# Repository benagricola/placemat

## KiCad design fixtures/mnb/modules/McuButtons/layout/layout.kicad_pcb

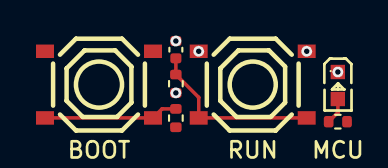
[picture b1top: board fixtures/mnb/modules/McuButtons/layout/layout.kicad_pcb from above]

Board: 2 copper layers, 7 parts (0 on the bottom side), 5 nets.

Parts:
C1: 100nF; C_0402_1005Metric
D1: KT-0603B; LED0603-RD_C2288
R1, R3: ERJ-2RKF1001X; R_0402_1005Metric
R2: ERJ-2RKF1800X; R_0402_1005Metric
SW1, SW2: TS-1187A-B-A-B; SW-SMD_4P-L5.1-W5.1-P3.70-LS6.5-TL_H1.5

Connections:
BOOT_SW: R1.2, SW1.1, SW1.2
STATUS_LED_A: D1.2, R2.2
boot_com: SW1.3, SW1.4
gnd: C1.1, D1.1, SW2.3, SW2.4
run: C1.2, R3.2, SW2.1, SW2.2

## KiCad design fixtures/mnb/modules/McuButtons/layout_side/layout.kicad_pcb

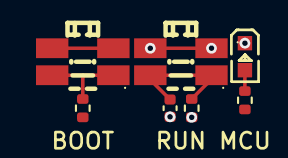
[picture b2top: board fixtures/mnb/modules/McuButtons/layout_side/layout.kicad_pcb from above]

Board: 2 copper layers, 7 parts (0 on the bottom side), 5 nets.

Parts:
C1: 100nF; C_0402_1005Metric
D1: KT-0603B; LED0603-RD_C2288
R1, R3: ERJ-2RKF1001X; R_0402_1005Metric
R2: ERJ-2RKF1800X; R_0402_1005Metric
SW1, SW2: EVQP7J01P; SW-SMD_EVQP7J01P

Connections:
BOOT_SW: R1.2, SW1.1, SW1.1'
STATUS_LED_A: D1.2, R2.2
boot_com: SW1.2, SW1.2'
gnd: C1.1, D1.1, SW2.2, SW2.2'
run: C1.2, R3.2, SW2.1, SW2.1'

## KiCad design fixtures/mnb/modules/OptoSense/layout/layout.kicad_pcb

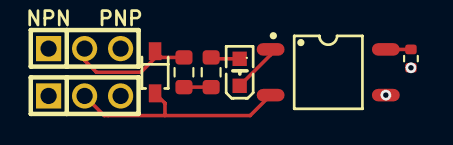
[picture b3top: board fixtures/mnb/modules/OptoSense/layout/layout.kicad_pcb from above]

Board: 2 copper layers, 8 parts (0 on the bottom side), 7 nets.

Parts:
D1: 1N4148WS; SOD-323_L1.8-W1.3-LS2.5-RD
D2: KT-0603Y; LED0603-R-RD_C2287
H1, H2: PZ200V-11-03P; HDR-TH_3P-P2.00-V-M
R1: ERJ-2RKF1002X; R_0402_1005Metric
R2, R3: ERJ-3EKF2201V; R_0603_1608Metric
U1: LTV-357T-C; SOP-4_L4.4-W3.9-P2.54-LS7.0-TL

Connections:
OPTO_AN: D2.2, U1.1
OPTO_ANSRC: D1.1, H1.2, R2.1
OPTO_CAT: D1.2, H2.2, U1.2
OPTO_LEDA: D2.1, R3.2
OPTO_RMID: R2.2, R3.1
gnd: H2.3, U1.3
out: R1.1, U1.4

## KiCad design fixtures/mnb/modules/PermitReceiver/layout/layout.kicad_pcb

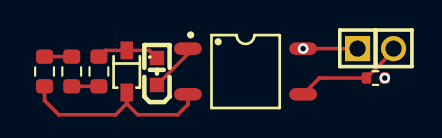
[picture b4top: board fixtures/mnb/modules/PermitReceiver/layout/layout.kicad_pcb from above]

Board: 2 copper layers, 8 parts (0 on the bottom side), 7 nets.

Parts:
D1: 1N4148WS; SOD-323_L1.8-W1.3-LS2.5-RD
D2: KT-0603R; LED-SMD_L1.6-W0.8-R-RD
H1: PZ200V-11-02P; HDR-TH_2P-P2.00-V-M
R1: ERJ-3EKF1002V; R_0603_1608Metric
R2: ERJ-2RKF1002X; R_0402_1005Metric
R3, R4: ERJ-3EKF2201V; R_0603_1608Metric
U1: LTV-357T-C; SOP-4_L4.4-W3.9-P2.54-LS7.0-TL

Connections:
PERMIT_AN: D1.1, D2.1, R4.2
PERMIT_OPTO_AN: D2.2, U1.1
PERMIT_RMID: R3.2, R4.1
out: H1.2, R2.1, U1.3
perm_n: D1.2, R1.2, U1.2
perm_p: R1.1, R3.1
v3v3: H1.1, U1.4

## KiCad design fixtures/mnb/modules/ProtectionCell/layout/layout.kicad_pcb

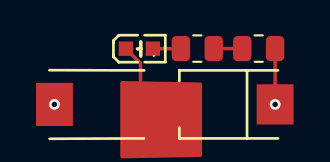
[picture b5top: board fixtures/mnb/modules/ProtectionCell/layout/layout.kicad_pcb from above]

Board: 2 copper layers, 5 parts (0 on the bottom side), 4 nets.

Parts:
D1: SS510B; SMB_L4.6-W3.5-LS5.3-RD
D2: SMBJ33CA; SMB_L4.6-W3.6-LS5.3-BI
D3: KT-0603Y; LED0603-R-RD_C2287
R1, R2: RC0805FR-071K3L; R_0805_2012Metric

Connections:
PROT_LED_MID: D3.1, R2.2
PROT_LED_RMID: R1.2, R2.1
v_out: D1.2, D2.1, D3.2
v_supply: D1.1, R1.1

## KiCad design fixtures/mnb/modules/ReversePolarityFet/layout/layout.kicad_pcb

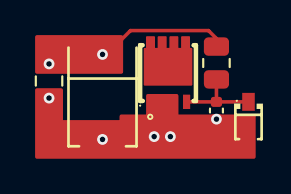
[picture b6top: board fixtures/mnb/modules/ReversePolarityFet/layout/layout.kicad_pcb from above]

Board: 2 copper layers, 6 parts (0 on the bottom side), 3 nets.

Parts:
C1: GCM155R71H104KE02D; C_0402_1005Metric
C2: GRM21BC72A105KE01L; C_0805_2012Metric
D1: BZT52B12S; SOD-323_L1.8-W1.3-LS2.5-RD
D2: SMBJ58A-TR; SMB_L4.6-W3.6-LS5.3-RD
Q1: ZH014T2G-L; DFN-8_L3.1-W3.1-P0.65-LS3.4-BL-1
R1: RC0805FR-0747KL; R_0805_2012Metric

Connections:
GATE: C1.1, D1.1, Q1.4, R1.2
gnd: C1.2, C2.2, D1.2, D2.2, Q1.1, Q1.2, Q1.3
v48: C2.1, D2.1, R1.1
